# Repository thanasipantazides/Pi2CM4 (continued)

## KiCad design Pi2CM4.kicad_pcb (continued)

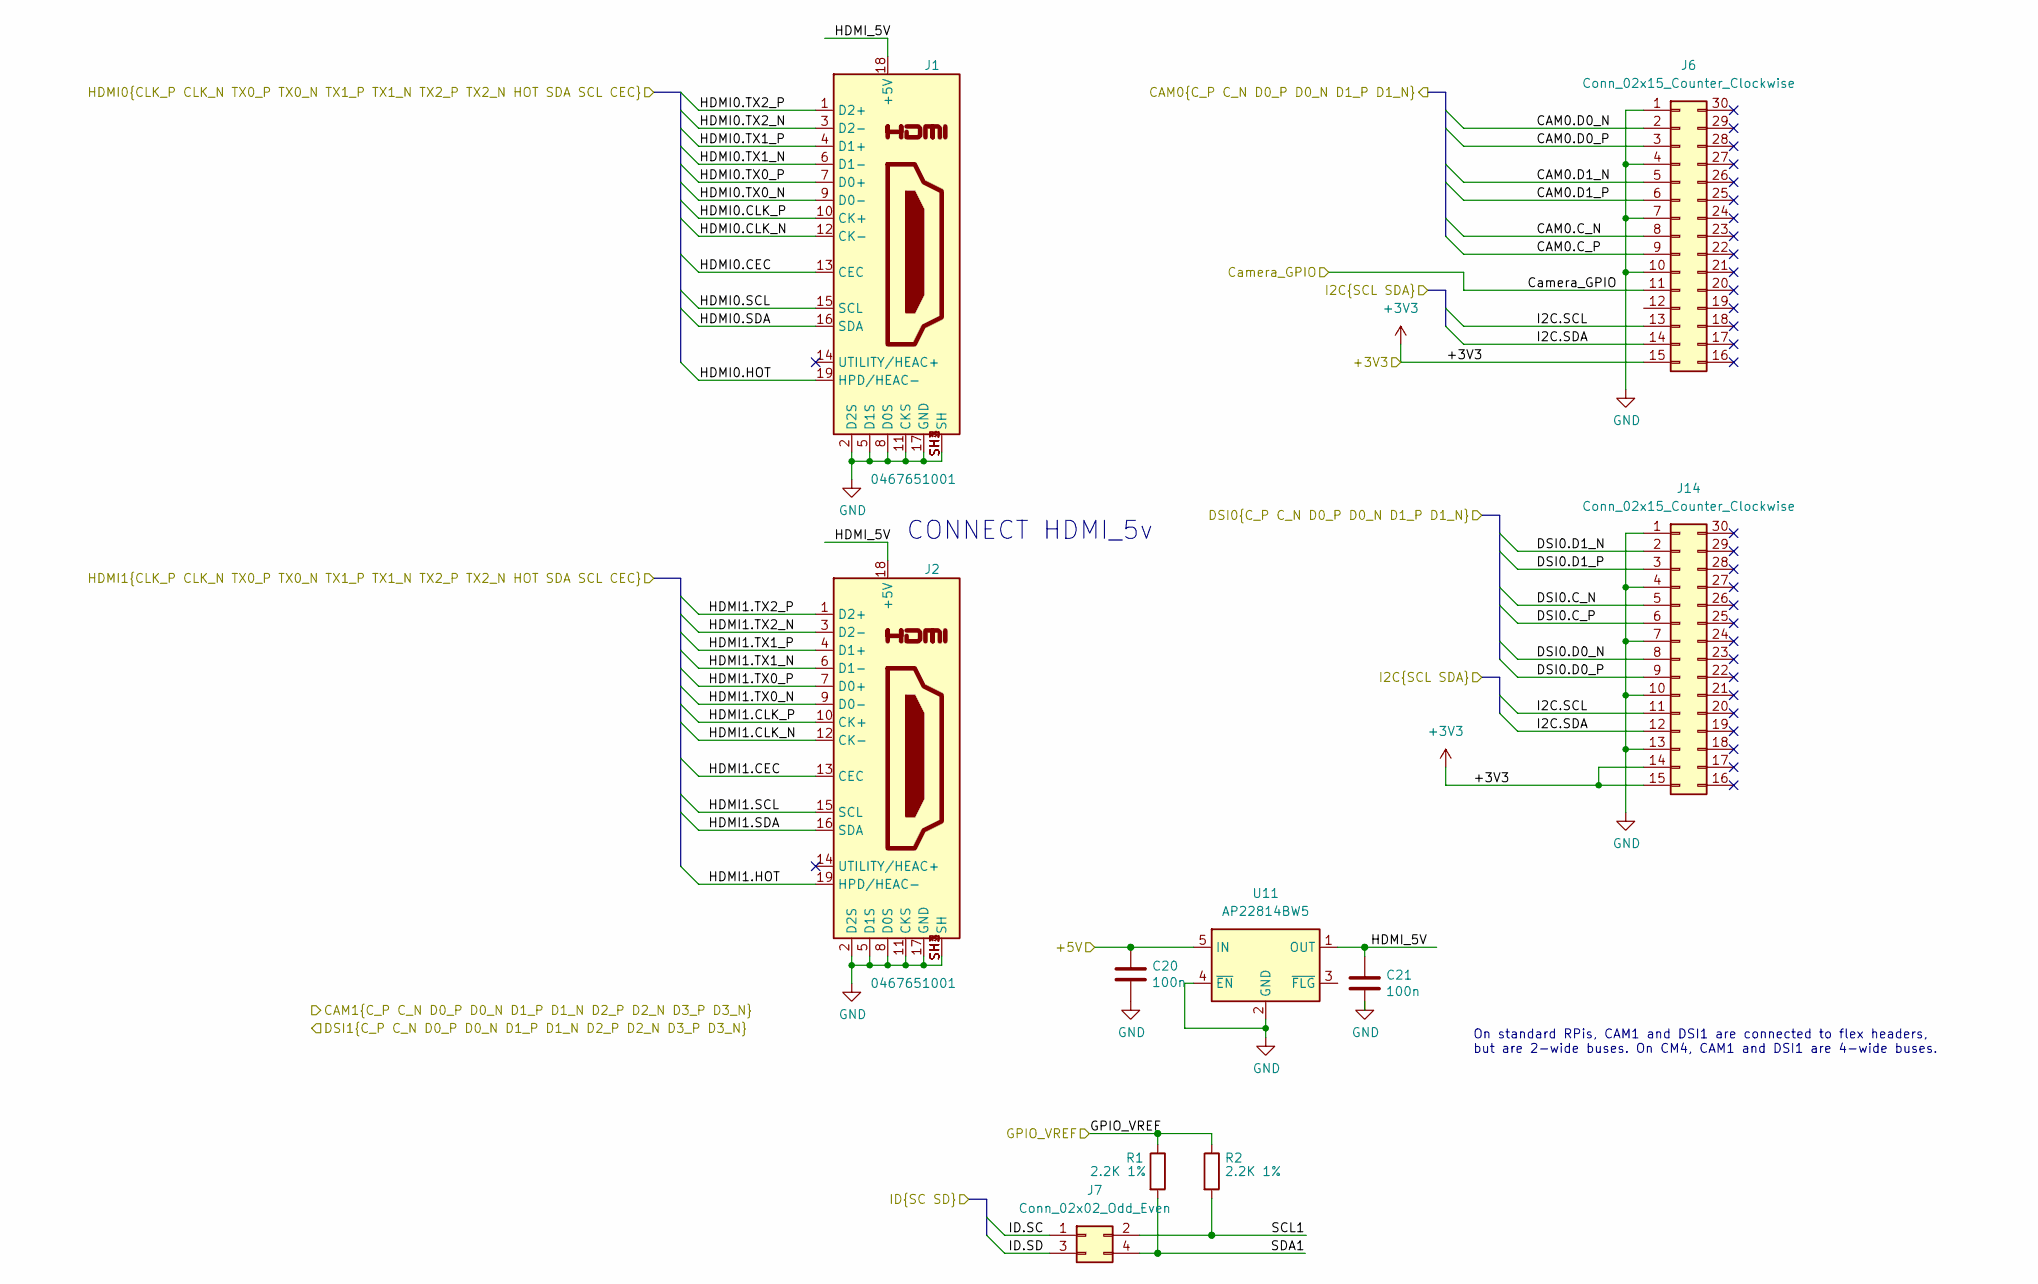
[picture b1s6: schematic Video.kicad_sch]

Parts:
C20, C21: 100n; C_0402_1005Metric; Part Description 0.1uF 10% 16V Ceramic Capacitor X7R 040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
J1, J2: 0467651001; HDMI_Micro-D_Molex_46765-1x01; Part Description HDMI Connector, Right Angle, 19 Contact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
J6, J14: Conn_02x15_Counter_Clockwise; Molex_052610-1572_2x15-1MP_P1.0mm_Vertical
J7: Conn_02x02_Odd_Even; PinSocket_2x02_P2.54mm_Vertical
R1, R2: 2.2K 1%; R_0402_1005Metric; Part Description Resistor 2.2K M1005 1% 63mW
U11: AP22814BW5; SOT-23-5

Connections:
+3V3: J6.15, J14.14, J14.15; also elsewhere on the board
+5V: C20.1, U11.5 (IN); also elsewhere on the board
/CM4/CAM0.C_N: J6.8; also elsewhere on the board
/CM4/CAM0.C_P: J6.9; also elsewhere on the board
/CM4/CAM0.D0_N: J6.2; also elsewhere on the board
/CM4/CAM0.D0_P: J6.3; also elsewhere on the board
/CM4/CAM0.D1_N: J6.5; also elsewhere on the board
/CM4/CAM0.D1_P: J6.6; also elsewhere on the board
/CM4/Camera_GPIO: J6.11; also elsewhere on the board
/CM4/DSI0.C_N: J14.5; also elsewhere on the board
/CM4/DSI0.C_P: J14.6; also elsewhere on the board
/CM4/DSI0.D0_N: J14.8; also elsewhere on the board
/CM4/DSI0.D0_P: J14.9; also elsewhere on the board
/CM4/DSI0.D1_N: J14.2; also elsewhere on the board
/CM4/DSI0.D1_P: J14.3; also elsewhere on the board
/CM4/GPIO_VREF: R1.1, R2.1; also elsewhere on the board
/CM4/HDMI0.CEC: J1.13 (CEC); also elsewhere on the board
/CM4/HDMI0.CLK_N: J1.12 (CK-); also elsewhere on the board
/CM4/HDMI0.CLK_P: J1.10 (CK+); also elsewhere on the board
/CM4/HDMI0.HOT: J1.19 (HPD/HEAC-); also elsewhere on the board
/CM4/HDMI0.SCL: J1.15 (SCL); also elsewhere on the board
/CM4/HDMI0.SDA: J1.16 (SDA); also elsewhere on the board
/CM4/HDMI0.TX0_N: J1.9 (D0-); also elsewhere on the board
/CM4/HDMI0.TX0_P: J1.7 (D0+); also elsewhere on the board
/CM4/HDMI0.TX1_N: J1.6 (D1-); also elsewhere on the board
/CM4/HDMI0.TX1_P: J1.4 (D1+); also elsewhere on the board
/CM4/HDMI0.TX2_N: J1.3 (D2-); also elsewhere on the board
/CM4/HDMI0.TX2_P: J1.1 (D2+); also elsewhere on the board
/CM4/HDMI1.CEC: J2.13 (CEC); also elsewhere on the board
/CM4/HDMI1.CLK_N: J2.12 (CK-); also elsewhere on the board
/CM4/HDMI1.CLK_P: J2.10 (CK+); also elsewhere on the board
/CM4/HDMI1.HOT: J2.19 (HPD/HEAC-); also elsewhere on the board
/CM4/HDMI1.SCL: J2.15 (SCL); also elsewhere on the board
/CM4/HDMI1.SDA: J2.16 (SDA); also elsewhere on the board
/CM4/HDMI1.TX0_N: J2.9 (D0-); also elsewhere on the board
/CM4/HDMI1.TX0_P: J2.7 (D0+); also elsewhere on the board
/CM4/HDMI1.TX1_N: J2.6 (D1-); also elsewhere on the board
/CM4/HDMI1.TX1_P: J2.4 (D1+); also elsewhere on the board
/CM4/HDMI1.TX2_N: J2.3 (D2-); also elsewhere on the board
/CM4/HDMI1.TX2_P: J2.1 (D2+); also elsewhere on the board
/CM4/I2C.SCL: J6.13, J14.11; also elsewhere on the board
/CM4/I2C.SDA: J6.14, J14.12; also elsewhere on the board
/CM4/ID.SC: J7.1; also elsewhere on the board
/CM4/ID.SD: J7.3; also elsewhere on the board
/Video/HDMI_5V: C21.1, J1.18 (+5V), J2.18 (+5V), U11.1 (OUT)
/Video/SCL1: J7.2, R2.2
/Video/SDA1: J7.4, R1.2
GND: C20.2, C21.2, J1.2 (D2S), J1.5 (D1S), J1.8 (D0S), J1.11 (CKS), J1.17 (GND), J1.SH1 (SH), J1.SH2 (SH), J1.SH3 (SH), J1.SH4 (SH), J2.2 (D2S), J2.5 (D1S), J2.8 (D0S), J2.11 (CKS), J2.17 (GND), J2.SH1 (SH), J2.SH2 (SH), J2.SH3 (SH), J2.SH4 (SH), J6.1, J6.4, J6.7, J6.10, J14.1, J14.4, J14.7, J14.10, J14.13, U11.2 (GND), U11.4 (~EN); also elsewhere on the board

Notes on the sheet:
CONNECT HDMI_5v
On standard RPis, CAM1 and DSI1 are connected to flex headers, but are 2-wide buses. On CM4, CAM1 and DSI1 are 4-wide buses.

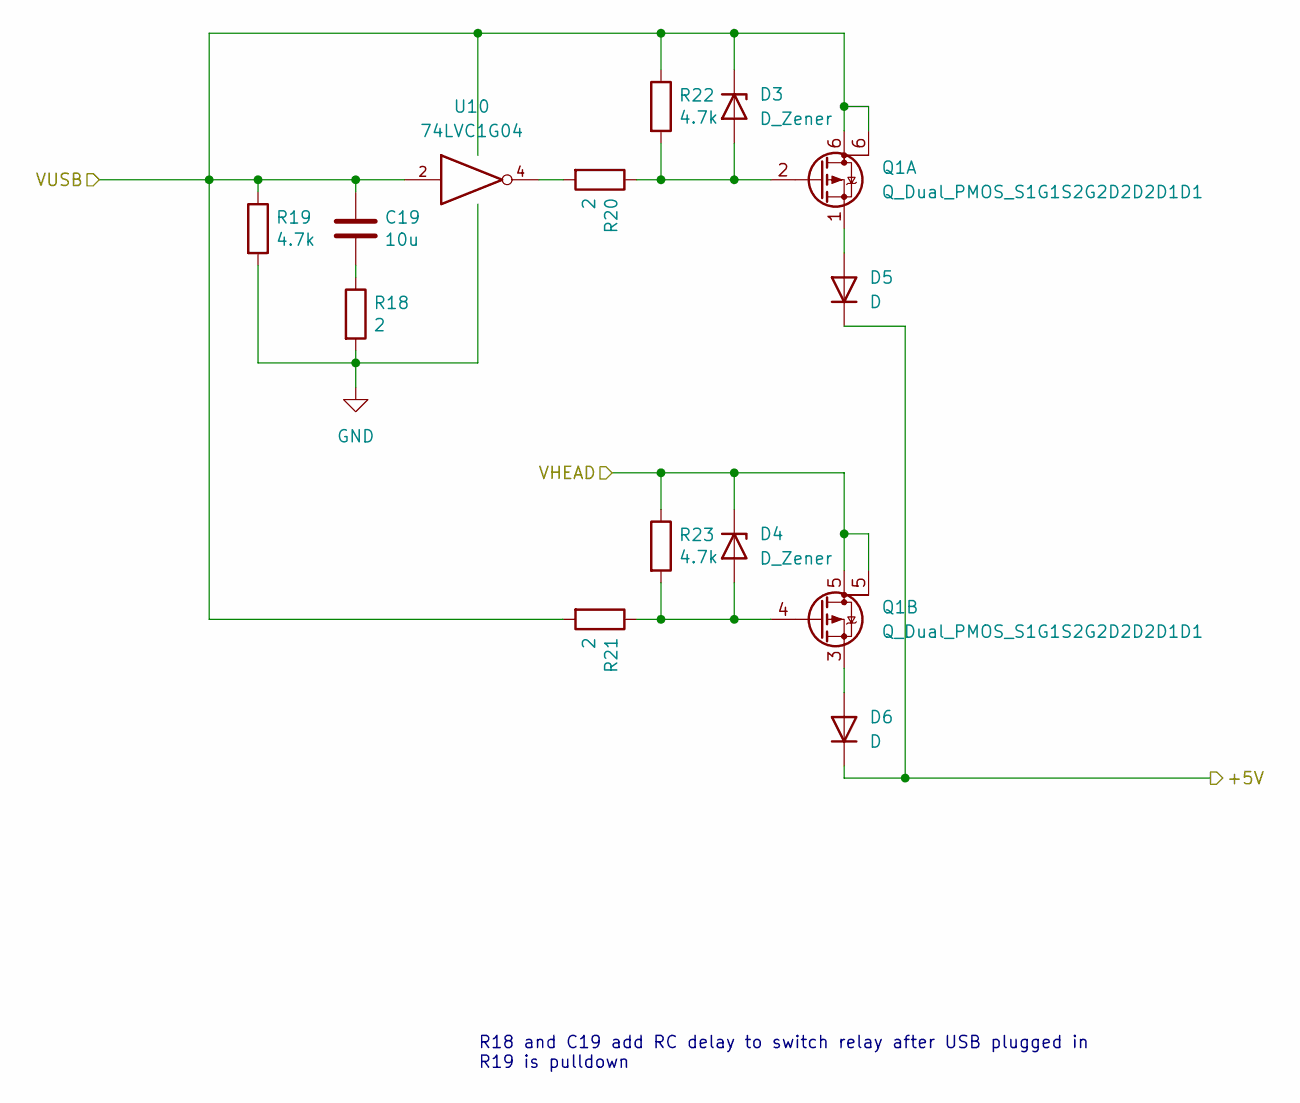
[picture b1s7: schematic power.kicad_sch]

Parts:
C19: 10u; C_0805_2012Metric; Part Description 10uF 10% 10V Ceramic Capacitor X7R 0805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
D3, D4: D_Zener; D_SOD-123
D5, D6: D; D_MELF
Q1: Q_Dual_PMOS_S1G1S2G2D2D2D1D1; PowerPAK_1212_Dual
R18, R20, R21: 2; R_2010_5025Metric; Part Description Resistor 1K M1005 1% 63mW
R19, R22, R23: 4.7k; R_0402_1005Metric; Part Description Resistor 1K M1005 1% 63mW
U10: 74LVC1G04; SOT-23-5

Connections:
+5V: D5.1 (K), D6.1 (K); also elsewhere on the board
/CM4/VHEAD: D4.1 (K), Q1.5 (D), R23.1; also elsewhere on the board
GND: R18.2, R19.2, U10.3 (GND); also elsewhere on the board
unnamed: C19.2, R18.1
unnamed: D3.2 (A), Q1.2 (G), R20.1, R22.2
unnamed: D4.2 (A), Q1.4 (G), R21.1, R23.2
unnamed: D5.2 (A), Q1.1 (S)
unnamed: D6.2 (A), Q1.3 (S)
unnamed: R20.2, U10.4
VCC: C19.1, D3.1 (K), Q1.6 (G), R19.1, R21.2, R22.1, U10.2, U10.5 (VCC)

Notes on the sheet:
R18 and C19 add RC delay to switch relay after USB plugged in R19 is pulldown

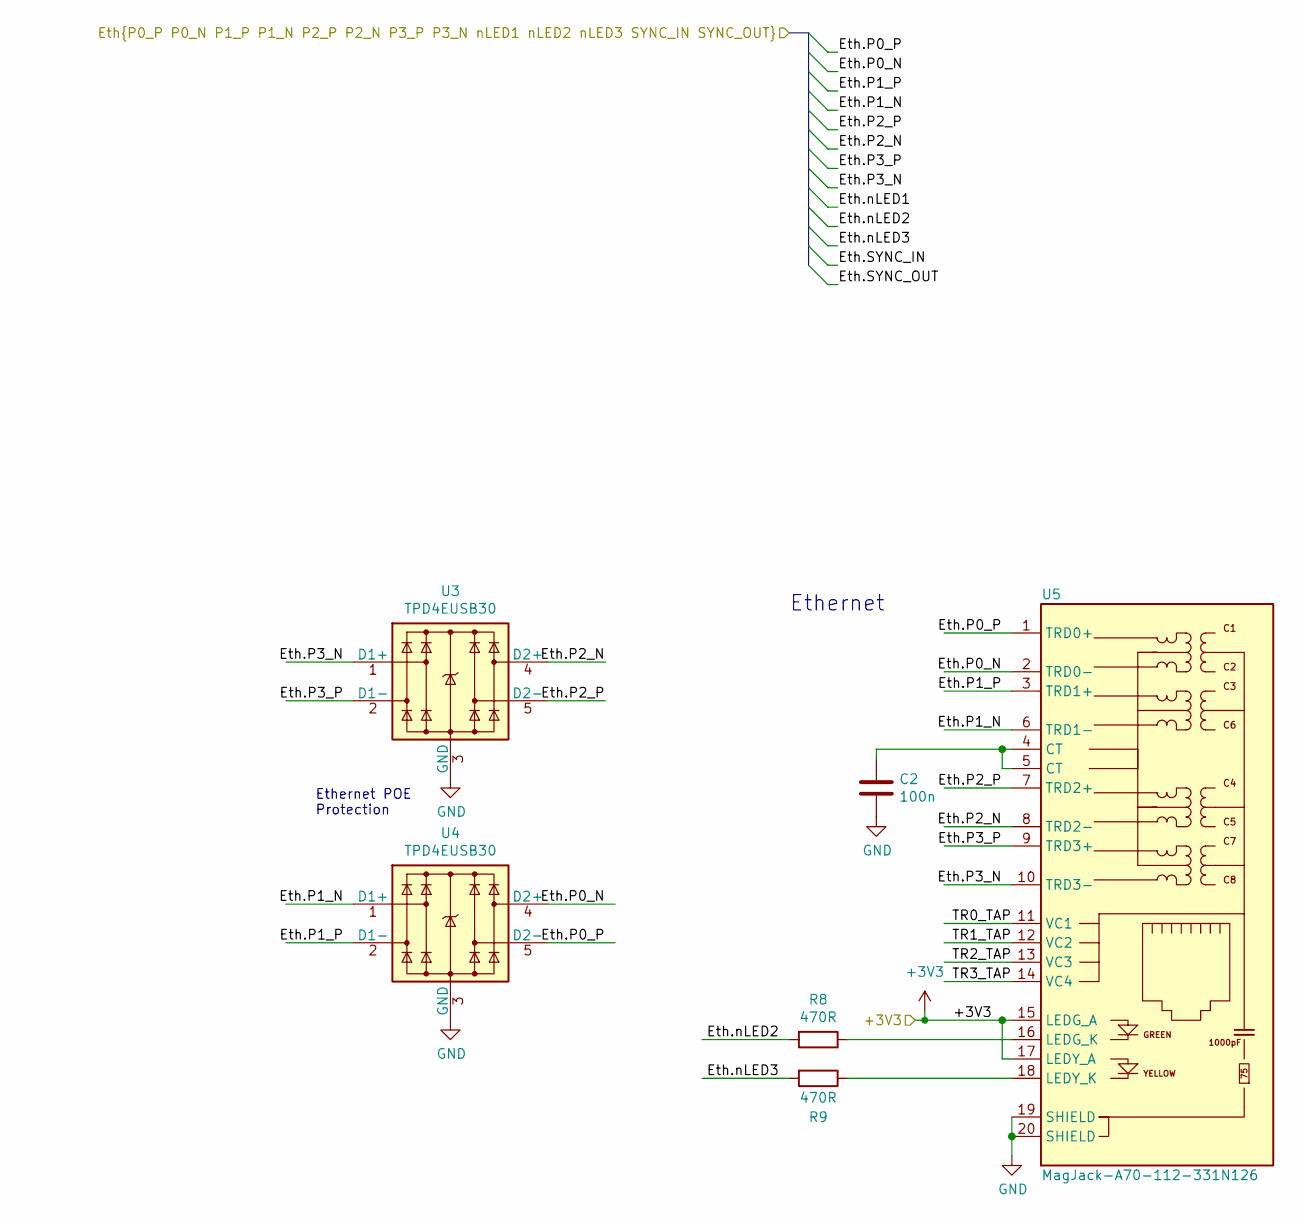
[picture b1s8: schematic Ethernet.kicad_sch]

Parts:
C2: 100n; C_0402_1005Metric; Part Description 0.1uF 10% 16V Ceramic Capacitor X7R 040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
R8, R9: 470R; R_0402_1005Metric; Part Description Resistor 470R M1005 1% 63mW
U3, U4: TPD4EUSB30; USON-10_2.5x1.0mm_P0.5mm; Part Description Quad TVS diode for high speed signals (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
U5: MagJack-A70-112-331N126; TRJG0926HENL; Part Description Gigabit Ethernet Magjack

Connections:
+3V3: U5.15 (LEDG_A), U5.17 (LEDY_A); also elsewhere on the board
/CM4/Eth.P0_N: U4.4 (D2+), U4.7, U5.2 (TRD0-); also elsewhere on the board
/CM4/Eth.P0_P: U4.5 (D2-), U4.6, U5.1 (TRD0+); also elsewhere on the board
/CM4/Eth.P1_N: U4.1 (D1+), U4.10, U5.6 (TRD1-); also elsewhere on the board
/CM4/Eth.P1_P: U4.2 (D1-), U4.9, U5.3 (TRD1+); also elsewhere on the board
/CM4/Eth.P2_N: U3.4 (D2+), U3.7, U5.8 (TRD2-); also elsewhere on the board
/CM4/Eth.P2_P: U3.5 (D2-), U3.6, U5.7 (TRD2+); also elsewhere on the board
/CM4/Eth.P3_N: U3.1 (D1+), U3.10, U5.10 (TRD3-); also elsewhere on the board
/CM4/Eth.P3_P: U3.2 (D1-), U3.9, U5.9 (TRD3+); also elsewhere on the board
/CM4/Eth.nLED2: R8.2; also elsewhere on the board
/CM4/Eth.nLED3: R9.2; also elsewhere on the board
/Ethernet/TR0_TAP: U5.11 (VC1)
/Ethernet/TR1_TAP: U5.12 (VC2)
/Ethernet/TR2_TAP: U5.13 (VC3)
/Ethernet/TR3_TAP: U5.14 (VC4)
GND: C2.2, U3.3 (GND), U3.8 (GND), U4.3 (GND), U4.8 (GND), U5.19 (SHIELD), U5.20 (SHIELD); also elsewhere on the board
unnamed: C2.1, U5.4 (CT), U5.5 (CT)
unnamed: R8.1, U5.16 (LEDG_K)
unnamed: R9.1, U5.18 (LEDY_K)

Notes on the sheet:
Ethernet
Ethernet POE Protection

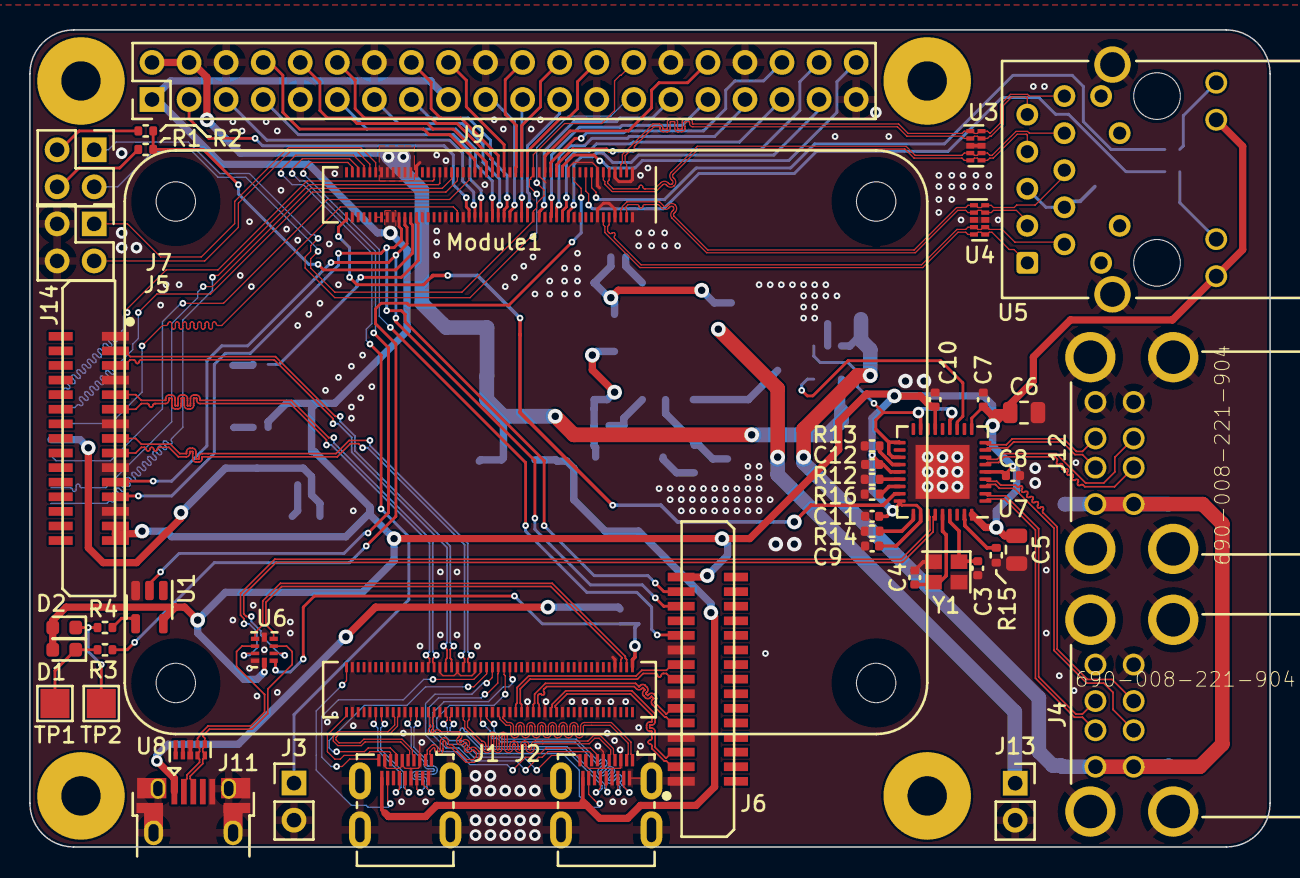
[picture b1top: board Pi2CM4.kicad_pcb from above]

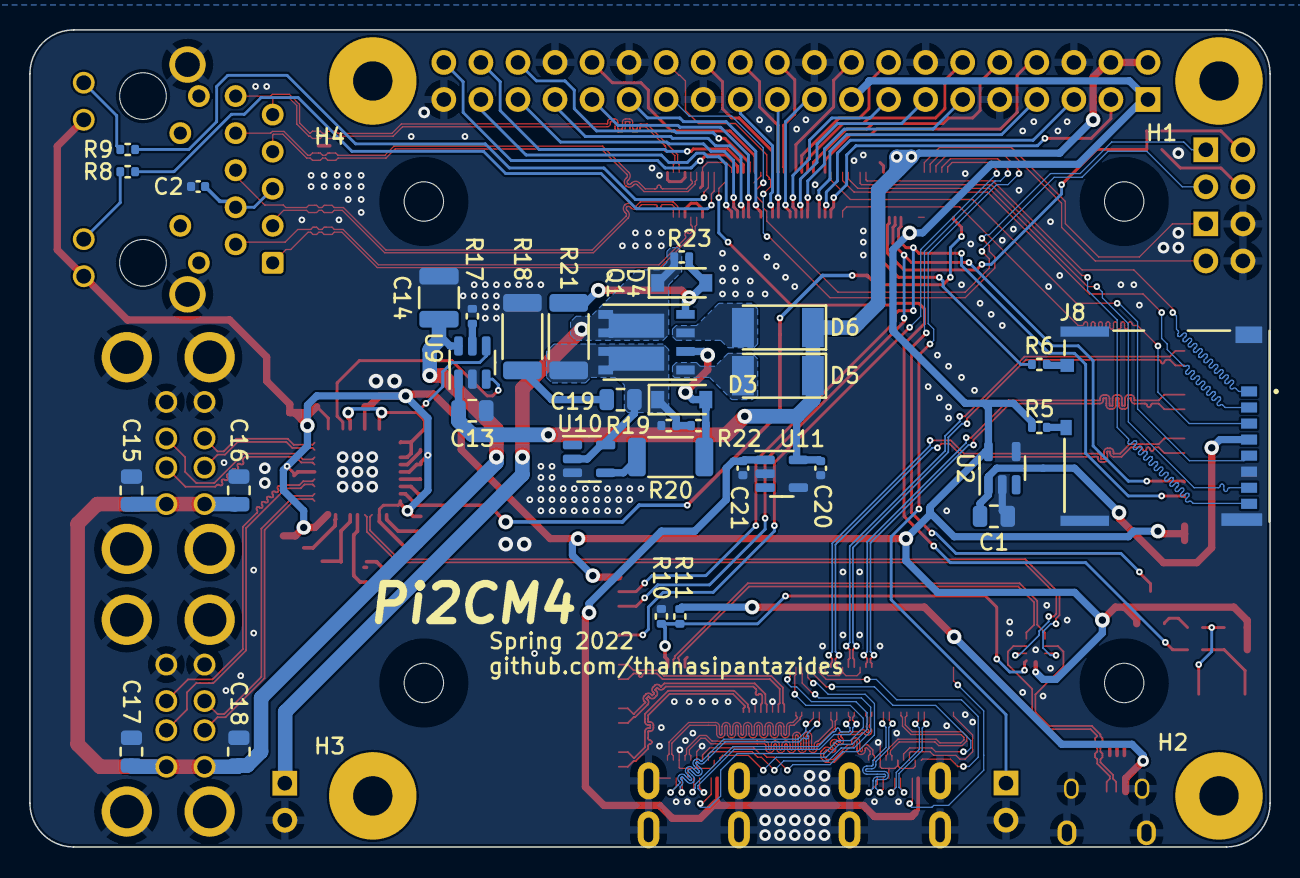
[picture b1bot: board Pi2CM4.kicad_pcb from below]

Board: 4 copper layers, 85.0 x 56.0 mm, 82 parts (34 on the bottom side), 144 nets.

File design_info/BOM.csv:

"Id";"Designator";"Package";"Quantity";"Designation";"Supplier and ref";
1;"Module1";"Raspberry-Pi-4-Compute-Module";1;"ComputeModule4";;;
2;"J11";"USB_Micro-B_EDAC_UCON00686";1;"USB_OTG";;;
3;"R15,R7";"R_0402_1005Metric";2;"12K 1%";;;
4;"J14,J6";"Molex_052610-1572_2x15-1MP_P1.0mm_Vertical";2;"Conn_02x15_Counter_Clockwise";;;
5;"R4,R3";"R_0402_1005Metric";2;"1k";;;
6;"C4,C3";"C_0402_1005Metric";2;"27pF";;;
7;"J2,J1";"HDMI_Micro-D_Molex_46765-1x01";2;"0467651001";;;
8;"C9,C20,C10,C11,C12,C8,C21,C7,C2";"C_0402_1005Metric";9;"100n";;;
9;"R13,R12,R16,R14";"R_0402_1005Metric";4;"36K 1%";;;
10;"R19,R23,R22";"R_0402_1005Metric";3;"4.7k";;;
11;"U6";"MSOP-10_3x3mm_P0.5mm";1;"FSUSB42MUX";;;
12;"TP2,TP1";"TestPoint_Pad_2.0x2.0mm";2;"TestPoint";;;
13;"H4";"MountingHole_2.7mm_M2.5";1;"hole";;;
14;"C18,C15,C5,C16,C17,C13,C6,C1,C19";"C_0805_2012Metric";9;"10u";;;
15;"D4,D3";"D_SOD-123";2;"D_Zener";;;
16;"U5";"TRJG0926HENL";1;"MagJack-A70-112-331N126";;;
17;"U8,U3,U4";"USON-10_2.5x1.0mm_P0.5mm";3;"TPD4EUSB30";;;
18;"Y1";"Crystal_SMD_2520-4Pin_2.5x2.0mm";1;"Crystal_GND24_Small";;;
19;"R18,R21,R20";"R_0402_1005Metric";3;"2";;;
20;"H3,H2,H1";"MountingHole_2.7mm_M2.5";3;"MountingHole";;;
21;"J12,J4";"MOLEX_USB_67298-4090";2;"690-008-221-904";;;
22;"J3";"PinHeader_1x02_P2.54mm_Vertical";1;"Conn_01x02";;;
23;"J13";"PinSocket_1x02_P2.54mm_Vertical";1;"Conn_01x02";;;
24;"C14";"C_1210_3225Metric";1;"100uF";;;
25;"R2,R1,R11,R10";"R_0402_1005Metric";4;"2.2K 1%";;;
26;"D1";"LED_0603_1608Metric";1;"LED Green";;;
27;"D2";"LED_0603_1608Metric";1;"LED Red";;;
28;"J7,J5";"PinSocket_2x02_P2.54mm_Vertical";2;"Conn_02x02_Odd_Even";;;
29;"U7";"QFN-36-1EP_6x6mm_P0.5mm_EP3.7x3.7mm";1;"USB2514B-I/M2";;;
30;"U1";"SOT-353_SC-70-5";1;"74LVC1G07SE-7";;;
31;"J9";"PinHeader_2x20_P2.54mm_Vertical";1;"header";;;
32;"U9";"SOT-23-6";1;"AP22653W6";;;
33;"U11";"SOT-23";1;"RT9742SNGV";;;
34;"R17";"R_0402_1005Metric";1;"15K 1%";;;
35;"R8,R9";"R_0402_1005Metric";2;"470R";;;
36;"D6,D5";"D_MELF";2;"D";;;
37;"U2";"SOT-23-5";1;"RT9742GGJ5";;;
38;"R5,R6";"R_0402_1005Metric";2;"nf";;;
39;"U10";"SOT-23-5";1;"74LVC1G04";;;
40;"Q1";"PowerPAK_1212_Dual";1;"Q_Dual_PMOS_S1G1S2G2D2D2D1D1";;;
41;"J8";"SDCARD_MOLEX_503398-1892";1;"Micro_SD_Card_Det";;;

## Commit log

2022-05-20 gitignore, readme
2022-05-20 removing garbage
2022-05-20 disclaimer
